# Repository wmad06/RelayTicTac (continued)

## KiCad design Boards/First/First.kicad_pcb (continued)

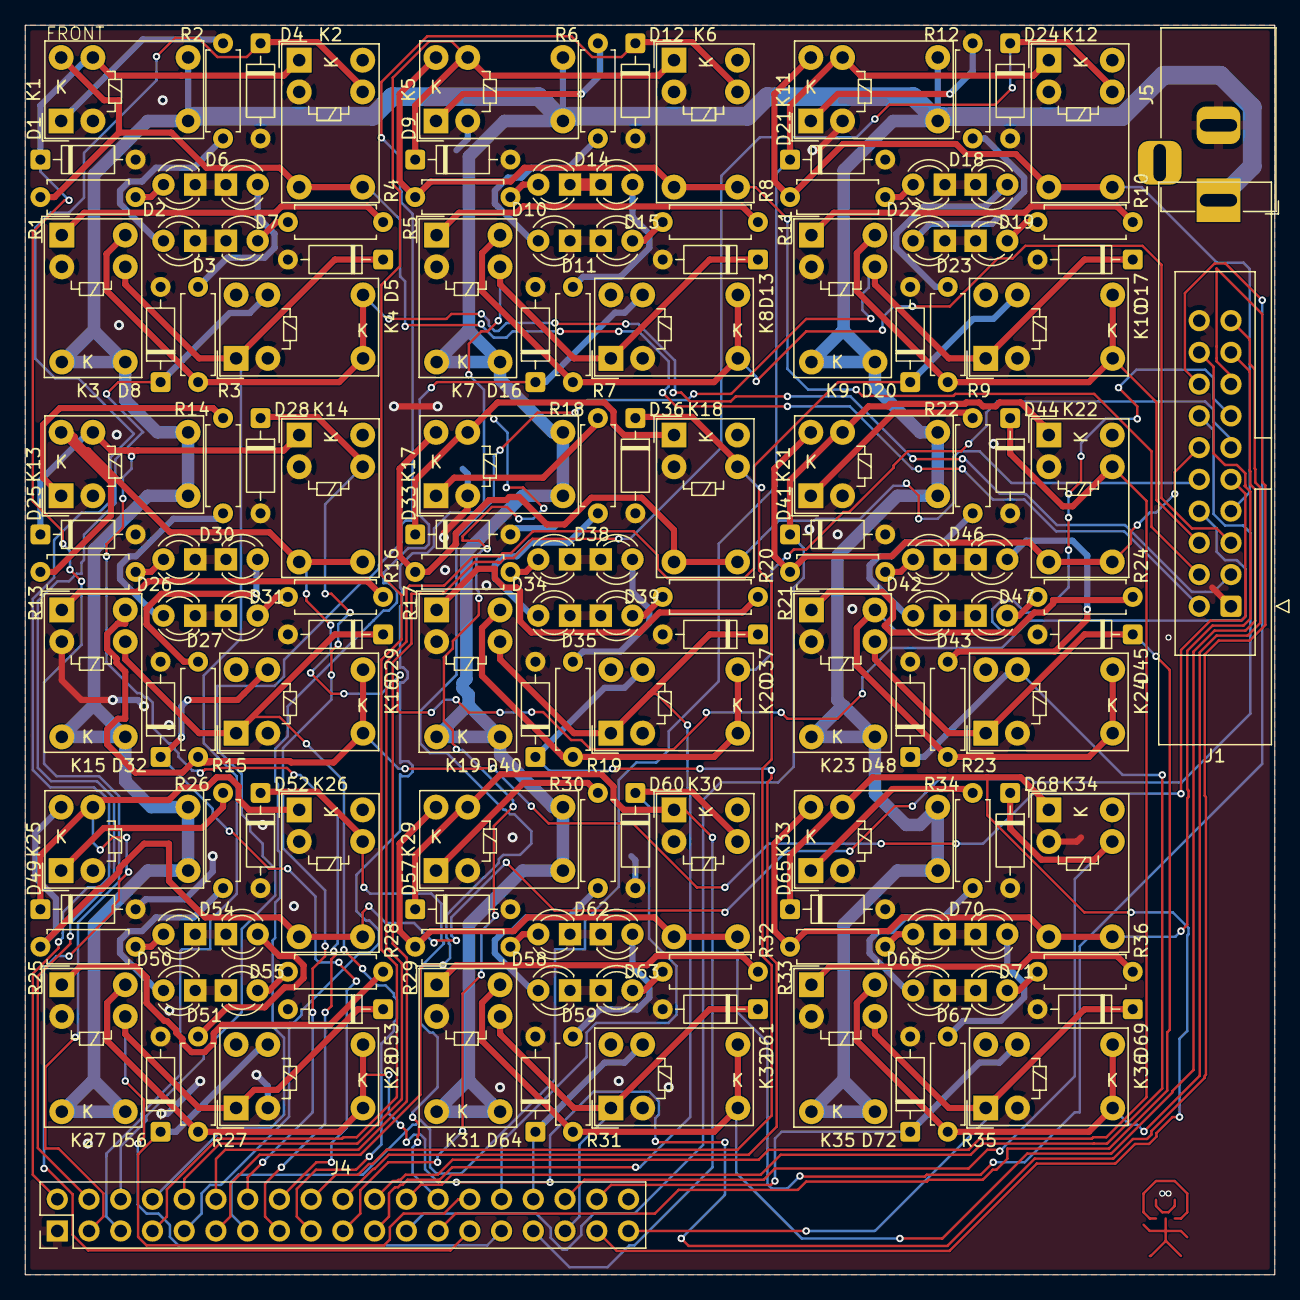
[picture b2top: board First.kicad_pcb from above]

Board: 2 copper layers, 100.0 x 100.0 mm, 148 parts (0 on the bottom side), 110 nets.

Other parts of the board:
U7: squareRegOutSilk
